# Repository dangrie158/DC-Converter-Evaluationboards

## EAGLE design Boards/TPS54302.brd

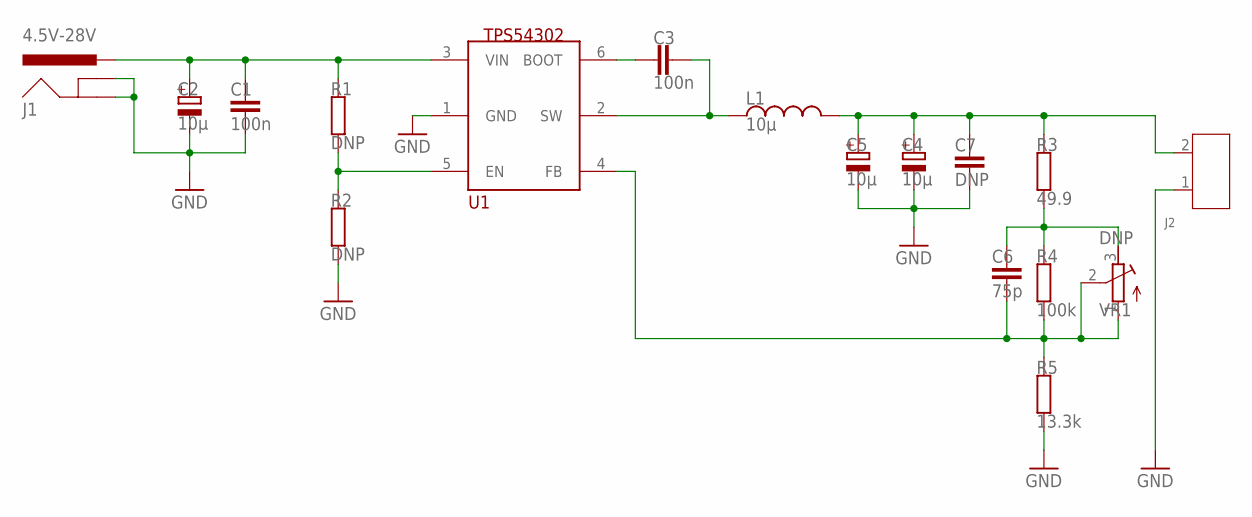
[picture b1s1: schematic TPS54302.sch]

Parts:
C1, C3: 100n; C0603K
C2, C4, C5: 10µ; 153CLV-0605
C6: 75p; C0603K
C7: DNP; C0603K
J1: 4.5V-28V; POWER_JACK_COMBO
J2: SCREW-TERMINAL-GREEN(2P-5.0); H2-5.0-10.5X8.0MM
L1: 10µ; INDDFN800X800X420-2N
R1, R2: DNP; R0603
R3: 49.9; R0603
R4: 100k; R0603
R5: 13.3k; R0603
U1: TPS54302; SOT95P280X110-6N
VR1: DNP; RTRIM64W

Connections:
BOOT: C3.1, U1.6 (BOOT)
EN: R1.1, R2.2, U1.5 (EN)
FB: C6.1, R4.1, R5.2, U1.4 (FB), VR1.1 (A), VR1.2 (S)
GND: C1.2, C2.-, C4.-, C5.-, C7.2, J1.GND (GNDBREAK), J1.GND@1 (GND), J1.GND@3 (GND), J1.GND@4 (GND), J2.1, R2.1, R5.1, U1.1 (GND)
unnamed: C6.2, R3.1, R4.2, VR1.3 (E)
SW: C3.2, L1.1, U1.2 (SW)
VIN: C1.1, C2.+, J1.POWER (PWR), J1.POWER@1 (PWR), J1.POWER@2 (PWR), R1.2, U1.3 (VIN)
VOUT: C4.+, C5.+, C7.1, J2.2, L1.2, R3.2

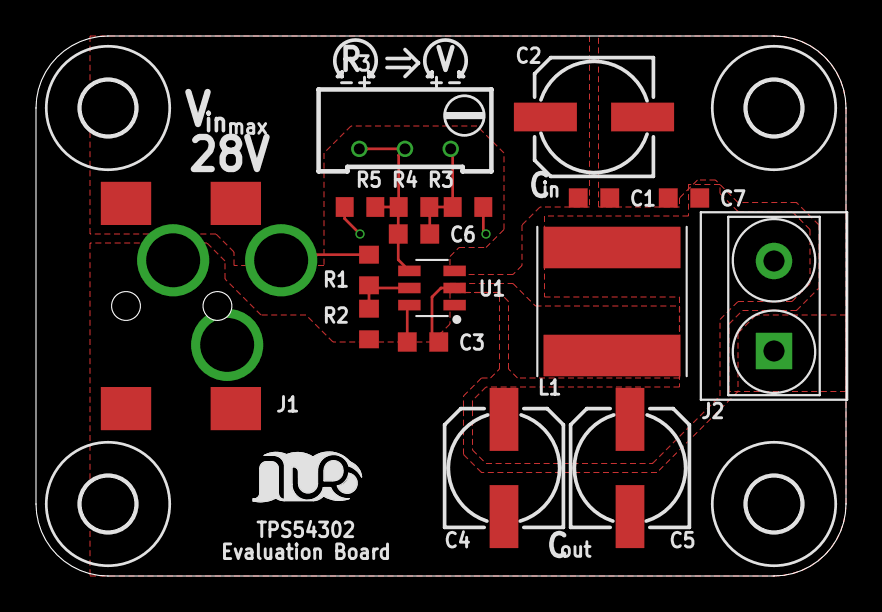
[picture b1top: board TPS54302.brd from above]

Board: 2 copper layers, 45.0 x 30.0 mm, 22 parts (0 on the bottom side), 8 nets.

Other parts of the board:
U$1, U$2, U$3, U$4: 3,0
U$5: LOGO-SILKSCREEEN-S

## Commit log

2020-01-09 initial commit for TPS54302
2020-01-09 cleaned up silkscreen
